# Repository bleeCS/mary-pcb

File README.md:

# mary-pcb
**WIP** 

# The Idea
After being a member of the mechanical keyboard community for about a year (not long, I know), I wanted to try to move into the design space. Realizing good PCB design becomes more difficult as the size of the board is increased, the goal for my first project is something smaller like a macro pad.

This board is meant to be a companion board for one of the most well-known TKL boards in the keyboard community. The board is a number pad with a little twist (I'm sorry, I couldn't stop myself from including this pun and will make more sense soon). I want the numpad to resemble a standard numpad that you will find on any full size keyboard, but have a function key that enables multiple layers of programmability (via QMK Firmware). There will also be a rotary encoder (ALPS EC11 as it seems to be the most popular and easily attainable for keyboard hobbyists) included on the numpad.

Before I committed to starting this project, I searched for macro pads with this layout and goal of being a companion board, but couldn't really find anything. So, I decided to move forward with the project.

# Renders
**FRONT:**

**BACK:**

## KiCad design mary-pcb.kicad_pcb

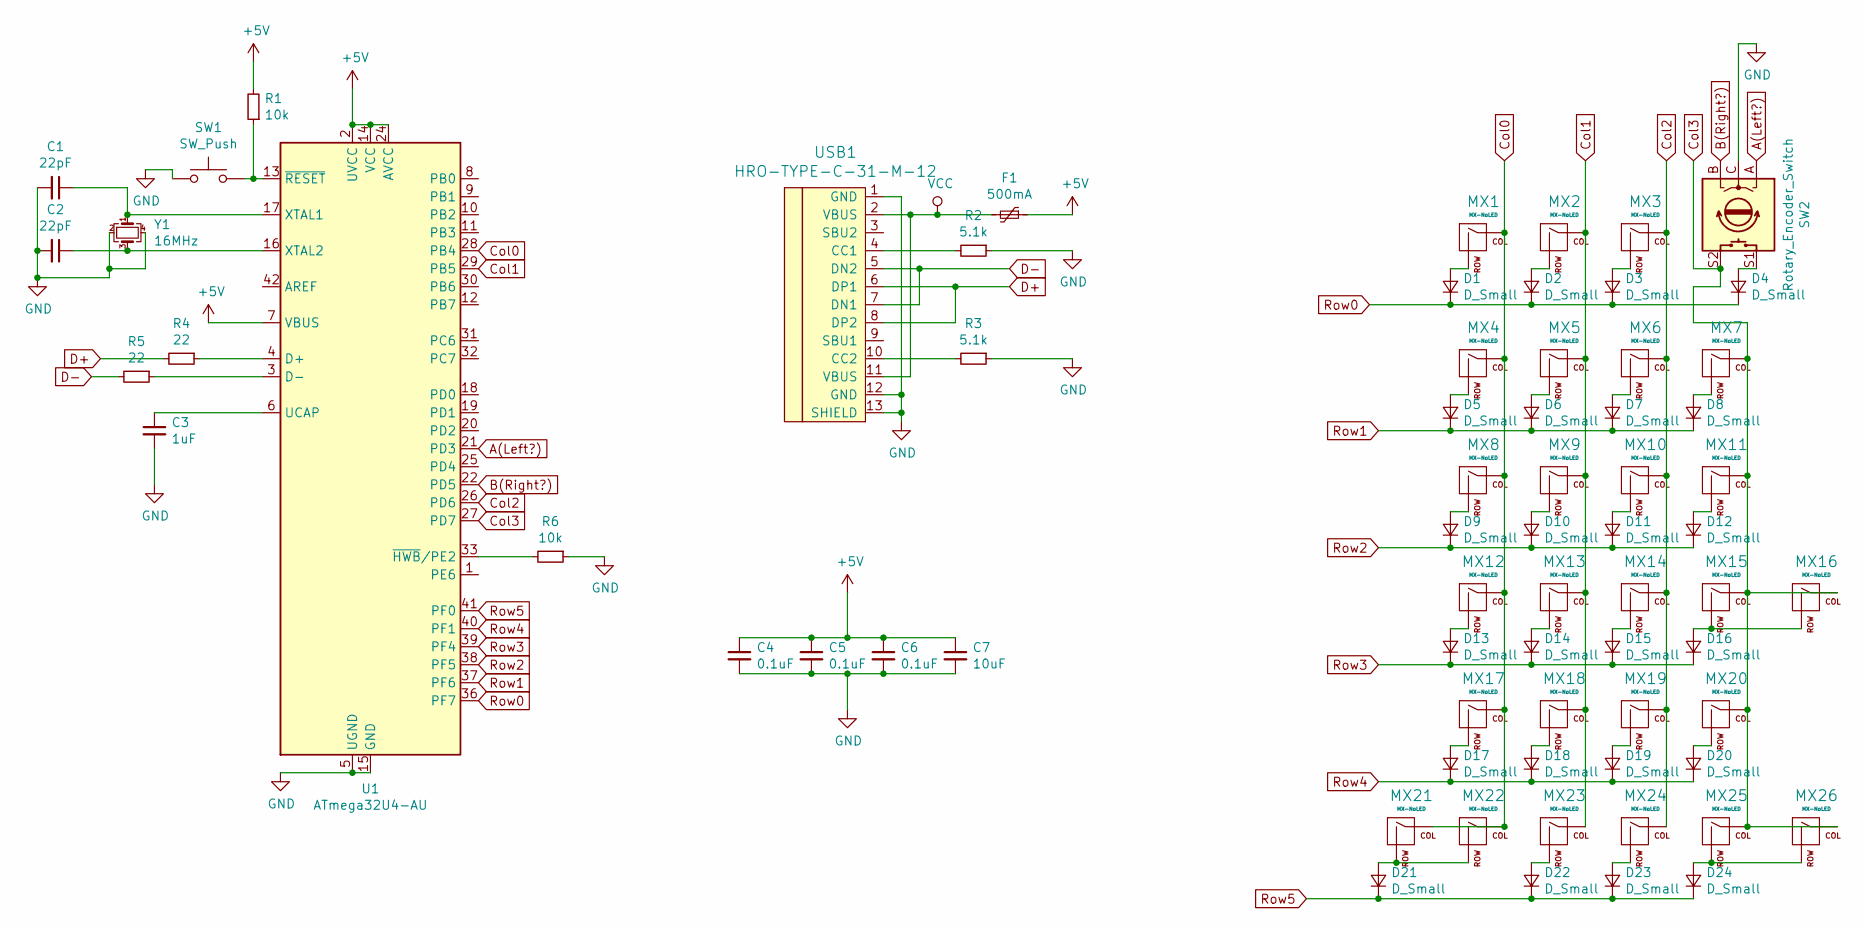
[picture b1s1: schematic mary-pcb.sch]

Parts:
C1, C2: 22pF; C_0805_2012Metric
C3: 1uF; C_0805_2012Metric
C4, C5, C6: 0.1uF; C_0805_2012Metric
C7: 10uF; C_0805_2012Metric
D1, D2, D3, D4, D5, D6, D7, D8, D9, D10, D11, D12, D13, D14, D15, D16, D17, D18, D19, D20, D21, D22, D23, D24: D_Small; D_SOD-123
F1: 500mA; Fuse_1206_3216Metric
MX1, MX2, MX3, MX4, MX5, MX6, MX7, MX8, MX9, MX10, MX11, MX12, MX13, MX14, MX15, MX17, MX18, MX19, MX20, MX22, MX23, MX24, MX25: MX-NoLED; MX-1U-NoLED
MX16, MX21, MX26: MX-NoLED; MX-2U-ReversedStabilizers-NoLED
R1, R6: 10k; R_0805_2012Metric
R2, R3: 5.1k; R_0805_2012Metric
R4, R5: 22; R_0805_2012Metric
SW1: SW_Push; SKQG-1155865
SW2: Rotary_Encoder_Switch; RotaryEncoder_EC11
U1: ATmega32U4-AU; TQFP-44_10x10mm_P0.8mm
USB1: HRO-TYPE-C-31-M-12
Y1: 16MHz; Crystal_SMD_3225-4Pin_3.2x2.5mm

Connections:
+5V: C4.1, C5.1, C6.1, C7.1, F1.1, R1.2, U1.2 (UVCC), U1.7 (VBUS), U1.14 (VCC), U1.24 (AVCC), U1.34 (VCC), U1.44 (AVCC); also elsewhere on the board
A(Left?): SW2.A, U1.21 (PD3)
B(Right?): SW2.B, U1.22 (PD5)
Col0: MX1.1 (COL), MX4.1 (COL), MX8.1 (COL), MX12.1 (COL), MX17.1 (COL), MX21.1 (COL), MX22.1 (COL), U1.28 (PB4)
Col1: MX2.1 (COL), MX5.1 (COL), MX9.1 (COL), MX13.1 (COL), MX18.1 (COL), MX23.1 (COL), U1.29 (PB5)
Col2: MX3.1 (COL), MX6.1 (COL), MX10.1 (COL), MX14.1 (COL), MX19.1 (COL), MX24.1 (COL), U1.26 (PD6)
Col3: MX7.1 (COL), MX11.1 (COL), MX15.1 (COL), MX16.1 (COL), MX20.1 (COL), MX25.1 (COL), MX26.1 (COL), SW2.S2, U1.27 (PD7)
D+: R4.2, USB1.6 (DP1), USB1.8 (DP2); also elsewhere on the board
D-: R5.2, USB1.5 (DN2), USB1.7 (DN1); also elsewhere on the board
GND: C1.2, C2.2, C3.2, C4.2, C5.2, C6.2, C7.2, R2.1, R3.1, R6.1, SW1.1, SW2.C, U1.5 (UGND), U1.15 (GND), U1.23 (GND), U1.35 (GND), U1.43 (GND), USB1.1 (GND), USB1.12 (GND), USB1.13 (SHIELD), Y1.2, Y1.4; also elsewhere on the board
unnamed: C1.1, U1.17 (XTAL1), Y1.1
unnamed: C2.1, U1.16 (XTAL2), Y1.3
unnamed: C3.1, U1.6 (UCAP)
unnamed: D1.2 (A), MX1.2 (ROW)
unnamed: D2.2 (A), MX2.2 (ROW)
unnamed: D3.2 (A), MX3.2 (ROW)
unnamed: D4.2 (A), SW2.S1
unnamed: D5.2 (A), MX4.2 (ROW)
unnamed: D6.2 (A), MX5.2 (ROW)
unnamed: D7.2 (A), MX6.2 (ROW)
unnamed: D8.2 (A), MX7.2 (ROW)
unnamed: D9.2 (A), MX8.2 (ROW)
unnamed: D10.2 (A), MX9.2 (ROW)
unnamed: D11.2 (A), MX10.2 (ROW)
unnamed: D12.2 (A), MX11.2 (ROW)
unnamed: D13.2 (A), MX12.2 (ROW)
unnamed: D14.2 (A), MX13.2 (ROW)
unnamed: D15.2 (A), MX14.2 (ROW)
unnamed: D16.2 (A), MX15.2 (ROW), MX16.2 (ROW)
unnamed: D17.2 (A), MX17.2 (ROW)
unnamed: D18.2 (A), MX18.2 (ROW)
unnamed: D19.2 (A), MX19.2 (ROW)
unnamed: D20.2 (A), MX20.2 (ROW)
unnamed: D21.2 (A), MX21.2 (ROW), MX22.2 (ROW)
unnamed: D22.2 (A), MX23.2 (ROW)
unnamed: D23.2 (A), MX24.2 (ROW)
unnamed: D24.2 (A), MX25.2 (ROW), MX26.2 (ROW)
unnamed: R1.1, SW1.2, U1.13 (~RESET)
unnamed: R2.2, USB1.4 (CC1)
unnamed: R3.2, USB1.10 (CC2)
unnamed: R4.1, U1.4 (D+)
unnamed: R5.1, U1.3 (D-)
unnamed: R6.2, U1.33 (~HWB~/PE2)
Row0: D1.1 (K), D2.1 (K), D3.1 (K), D4.1 (K), U1.36 (PF7)
Row1: D5.1 (K), D6.1 (K), D7.1 (K), D8.1 (K), U1.37 (PF6)
Row2: D9.1 (K), D10.1 (K), D11.1 (K), D12.1 (K), U1.38 (PF5)
Row3: D13.1 (K), D14.1 (K), D15.1 (K), D16.1 (K), U1.39 (PF4)
Row4: D17.1 (K), D18.1 (K), D19.1 (K), D20.1 (K), U1.40 (PF1)
Row5: D21.1 (K), D22.1 (K), D23.1 (K), D24.1 (K), U1.41 (PF0)
VCC: F1.2, USB1.2 (VBUS), USB1.11 (VBUS)

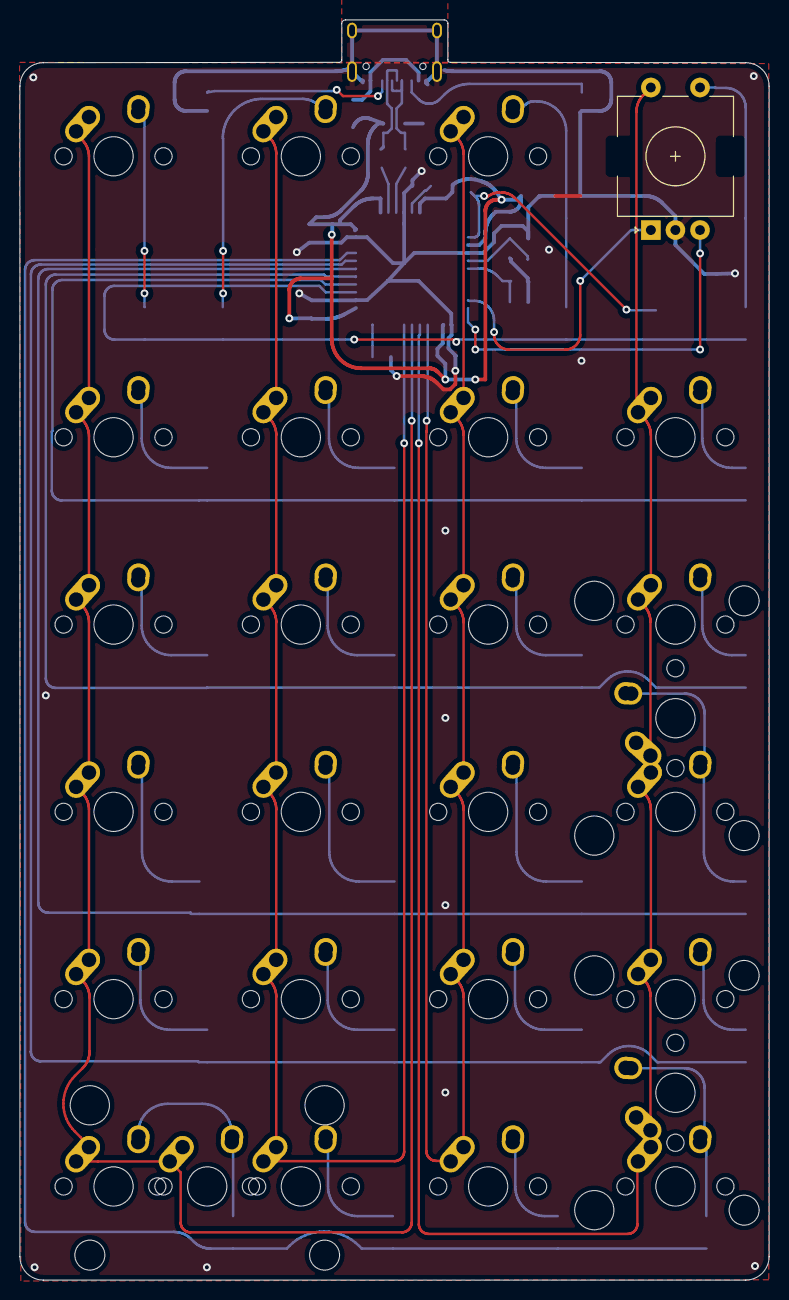
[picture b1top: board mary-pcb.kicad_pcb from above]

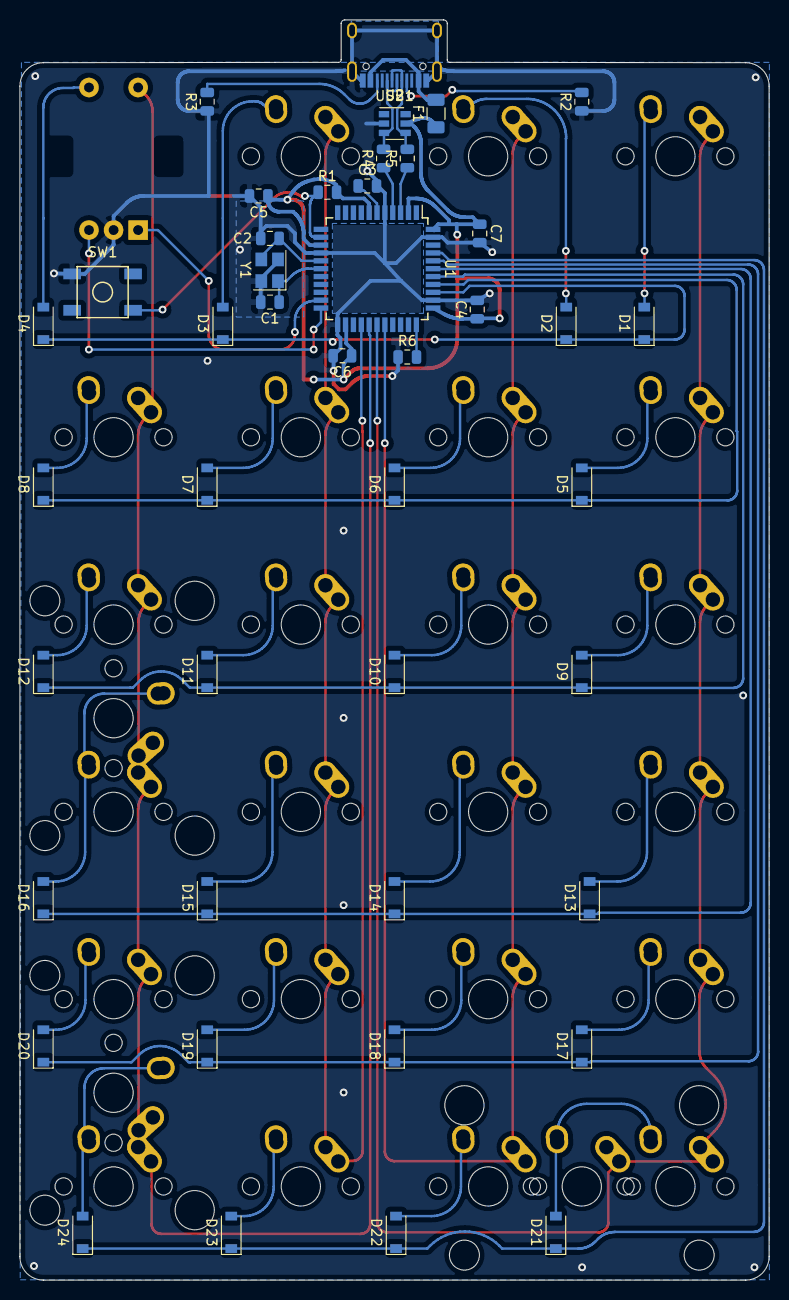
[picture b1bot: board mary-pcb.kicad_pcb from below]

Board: 2 copper layers, 76.2 x 128.2 mm, 70 parts (43 on the bottom side), 50 nets.

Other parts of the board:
U2: SRV05-4; SOT-23-6

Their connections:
+5V: U2.5; also elsewhere on the board
D+: U2.3; also elsewhere on the board
D-: U2.4; also elsewhere on the board
GND: U2.2; also elsewhere on the board

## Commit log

2019-12-31 initialize project files
2019-12-31 add submodules
2019-12-31 add footprint libraries
2019-12-31 add footprint library for rotary encoder
2020-01-01 add type c library
2020-01-01 begin schematic
2020-01-02 add MCU to schematic
2020-01-02 add usb c to schematic
2020-01-05 complete keyboard matrix
2020-01-06 assign footprints
2020-01-06 export pcb data
2020-01-28 place switches on pcb
2020-02-03 tentative rotary encoder placement
2020-02-10 fix switch placement
2020-02-11 update pcb footprints, place diodes
2020-02-12 place resistors, diodes, reset, capacitors
2020-02-15 complete routing
2020-02-27 complete routing, upload renders
2020-03-03 move usb
2020-03-10 add esd protection, ground pours, via stitching
2020-03-12 edit ground pours, via stitching, fuse placement
2020-03-12 fix drc error caused by via
